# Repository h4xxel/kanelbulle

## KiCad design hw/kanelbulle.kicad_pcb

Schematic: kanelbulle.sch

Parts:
C1, C2, C3, C4, C5, C6, C7, C8: C
D1, D2, D3, D4, D5, D6, D7, D8, D9, D10, D11, D12, D13, D14, D15, D16, D17, D18, D19, D20, D21, D22, D23, D24, D25, D26, D27, D28, D29, D30, D31, D32, D33, D34, D35, D36, D37, D38, D39, D40, D41, D42, D43, D44, D45, D46, D47, D48, D49, D50, D51: LED_RGB
P1: USB
P2: CONN_6
R1, R2, R3, R4, R5, R6, R7, R8, R9, R10, R11, R12, R13, R14, R15, R16, R17, R18, R19: R
U1: LPC1114/302
U2: PCA9685
U3, U4, U5: ULN2003A
U6: NCP1117ST33T3G

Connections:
3V3: C1.1, C2.1, C3.1, C4.1, C5.1, C6.1, C7.1, D1.1 (A), D2.1 (A), D3.1 (A), D4.1 (A), D5.1 (A), D6.1 (A), D7.1 (A), D8.1 (A), D9.1 (A), D10.1 (A), D11.1 (A), D12.1 (A), D13.1 (A), D14.1 (A), D15.1 (A), D16.1 (A), D17.1 (A), D18.1 (A), D19.1 (A), D20.1 (A), D21.1 (A), D22.1 (A), D23.1 (A), D24.1 (A), D25.1 (A), D26.1 (A), D27.1 (A), D28.1 (A), D29.1 (A), D30.1 (A), D31.1 (A), D32.1 (A), D33.1 (A), D34.1 (A), D35.1 (A), D36.1 (A), D37.1 (A), D38.1 (A), D39.1 (A), D40.1 (A), D41.1 (A), D42.1 (A), D43.1 (A), D44.1 (A), D45.1 (A), D46.1 (A), D47.1 (A), D48.1 (A), D49.1 (A), D50.1 (A), D51.1 (A), P2.6, R1.1, R2.1, R3.1, R4.1, U1.8 (VDD), U1.44 (VDD), U2.1 (A0), U2.3 (A2), U2.5 (A4), U2.28 (VDD), U6.2 (VO)
+5V: C8.1, P1.4, U6.3 (VI)
/B1: D1.4 (B), D2.4 (B), D3.4 (B), D4.4 (B), D5.4 (B), D6.4 (B), D7.4 (B), D8.4 (B), D9.4 (B), D10.4 (B), D11.4 (B), D12.4 (B), D13.4 (B), D14.4 (B), D15.4 (B), D16.4 (B), D17.4 (B), D18.4 (B), D19.4 (B), D20.4 (B), R15.2
/B2: D21.4 (B), D22.4 (B), D23.4 (B), D24.4 (B), D25.4 (B), D26.4 (B), D27.4 (B), D28.4 (B), D29.4 (B), D30.4 (B), D31.4 (B), D32.4 (B), D33.4 (B), D34.4 (B), D35.4 (B), R16.2
/B3: D36.4 (B), D37.4 (B), D38.4 (B), D39.4 (B), D40.4 (B), D41.4 (B), D42.4 (B), D43.4 (B), D44.4 (B), D45.4 (B), R17.2
/B4: D46.4 (B), D47.4 (B), D48.4 (B), D49.4 (B), D50.4 (B), R18.2
/B5: D51.4 (B), R19.2
/G1: D1.3 (G), D2.3 (G), D3.3 (G), D4.3 (G), D5.3 (G), D6.3 (G), D7.3 (G), D8.3 (G), D9.3 (G), D10.3 (G), D11.3 (G), D12.3 (G), D13.3 (G), D14.3 (G), D15.3 (G), D16.3 (G), D17.3 (G), D18.3 (G), D19.3 (G), D20.3 (G), R10.2
/G2: D21.3 (G), D22.3 (G), D23.3 (G), D24.3 (G), D25.3 (G), D26.3 (G), D27.3 (G), D28.3 (G), D29.3 (G), D30.3 (G), D31.3 (G), D32.3 (G), D33.3 (G), D34.3 (G), D35.3 (G), R11.2
/G3: D36.3 (G), D37.3 (G), D38.3 (G), D39.3 (G), D40.3 (G), D41.3 (G), D42.3 (G), D43.3 (G), D44.3 (G), D45.3 (G), R12.2
/G4: D46.3 (G), D47.3 (G), D48.3 (G), D49.3 (G), D50.3 (G), R13.2
/G5: D51.3 (G), R14.2
/ISP: P2.2, R1.2, U1.4 (~ISP_EN)
/LEDOE: U1.14 (PIO0_3), U2.23 (~OE)
/R1: D1.2 (R), D2.2 (R), D3.2 (R), D4.2 (R), D5.2 (R), D6.2 (R), D7.2 (R), D8.2 (R), D9.2 (R), D10.2 (R), D11.2 (R), D12.2 (R), D13.2 (R), D14.2 (R), D15.2 (R), D16.2 (R), D17.2 (R), D18.2 (R), D19.2 (R), D20.2 (R), R5.2
/R2: D21.2 (R), D22.2 (R), D23.2 (R), D24.2 (R), D25.2 (R), D26.2 (R), D27.2 (R), D28.2 (R), D29.2 (R), D30.2 (R), D31.2 (R), D32.2 (R), D33.2 (R), D34.2 (R), D35.2 (R), R6.2
/R3: D36.2 (R), D37.2 (R), D38.2 (R), D39.2 (R), D40.2 (R), D41.2 (R), D42.2 (R), D43.2 (R), D44.2 (R), D45.2 (R), R7.2
/R4: D46.2 (R), D47.2 (R), D48.2 (R), D49.2 (R), D50.2 (R), R8.2
/R5: D51.2 (R), R9.2
/RST: P2.1, R2.2, U1.3 (~RESET)
/RX: P2.4, U1.46 (PIO1_6/RXD)
/SCL: R4.2, U1.15 (PIO0_4), U2.26 (SCL)
/SDA: R3.2, U1.16 (PIO0_5), U2.27 (SDA)
/TX: P2.3, U1.47 (PIO1_7/TXD)
GND: C1.2, C2.2, C3.2, C4.2, C5.2, C6.2, C7.2, C8.2, P1.1, P1.GND, P2.5, U1.5 (VSS), U1.41 (VSS), U2.2 (A1), U2.4 (A3), U2.14 (VSS), U2.24 (A5), U2.25 (EXTCLK), U3.6 (I6), U3.7 (I7), U3.8 (GND), U4.6 (I6), U4.7 (I7), U4.8 (GND), U5.6 (I6), U5.7 (I7), U5.8 (GND), U6.1 (GND)
unnamed: R14.1, U4.12 (O5)
unnamed: R5.1, U3.16 (O1)
unnamed: R6.1, U3.15 (O2)
unnamed: R7.1, U3.14 (O3)
unnamed: R8.1, U3.13 (O4)
unnamed: R9.1, U3.12 (O5)
unnamed: R10.1, U4.16 (O1)
unnamed: R11.1, U4.15 (O2)
unnamed: R12.1, U4.14 (O3)
unnamed: R13.1, U4.13 (O4)
unnamed: U2.7 (LED1), U3.2 (I2)
unnamed: U2.6 (LED0), U3.1 (I1)
unnamed: U2.11 (LED5), U4.1 (I1)
unnamed: U2.10 (LED4), U3.5 (I5)
unnamed: U2.9 (LED3), U3.4 (I4)
unnamed: U2.8 (LED2), U3.3 (I3)
unnamed: R15.1, U5.16 (O1)
unnamed: R16.1, U5.15 (O2)
unnamed: U2.15 (LED8), U4.4 (I4)
unnamed: U2.18 (LED11), U5.2 (I2)
unnamed: U2.17 (LED10), U5.1 (I1)
unnamed: U2.16 (LED9), U4.5 (I5)
unnamed: U2.13 (LED7), U4.3 (I3)
unnamed: U2.12 (LED6), U4.2 (I2)
unnamed: U2.21 (LED14), U5.5 (I5)
unnamed: U2.20 (LED13), U5.4 (I4)
unnamed: U2.19 (LED12), U5.3 (I3)
unnamed: R19.1, U5.12 (O5)
unnamed: R18.1, U5.13 (O4)
unnamed: R17.1, U5.14 (O3)

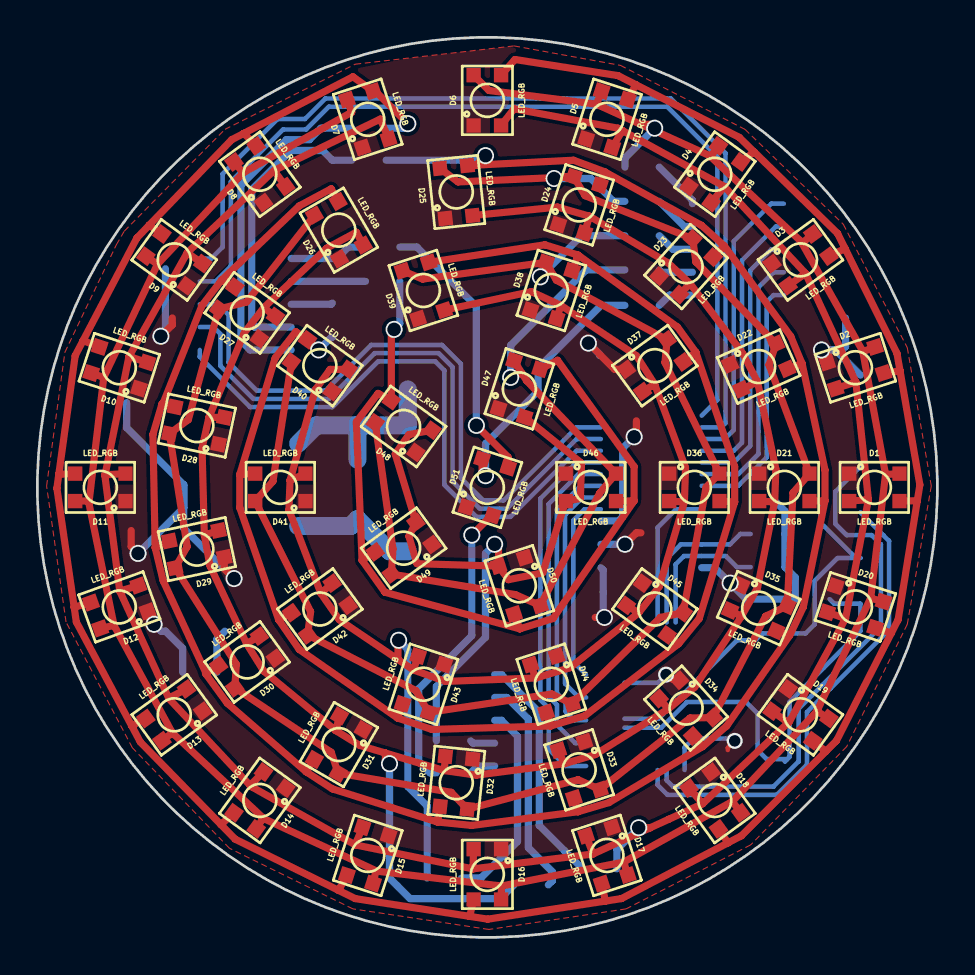
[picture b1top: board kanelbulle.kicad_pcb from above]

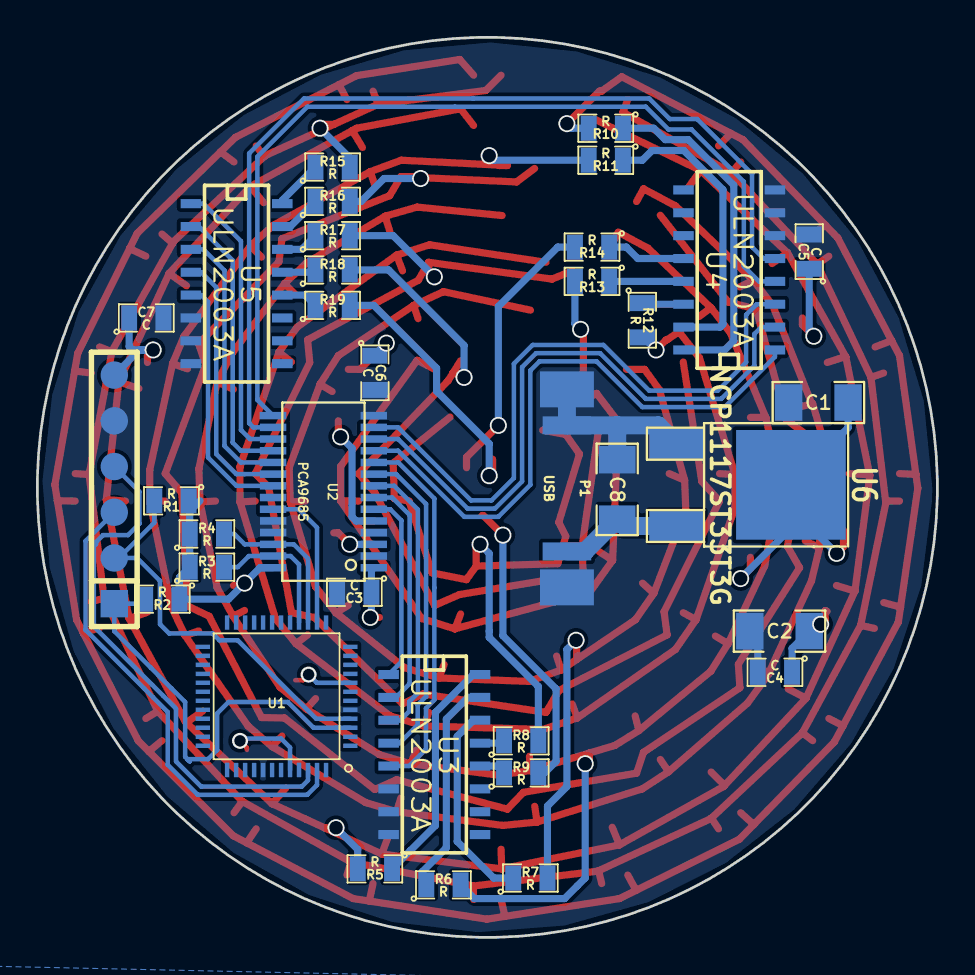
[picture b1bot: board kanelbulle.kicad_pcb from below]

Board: 2 copper layers, 50.0 x 50.0 mm, 86 parts (35 on the bottom side), 55 nets.

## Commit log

2015-01-28 gitignore
2015-01-28 hardware placeholder
2015-01-28 added micro controller to schematic
2015-01-28 leds, leds everywhere
2015-01-29 added led driver chip
2015-01-29 added led 3d model
2015-01-29 lqfp 3d model
2015-02-01 Moved all LEDs
2015-02-02 connected leds on schematic
2015-02-02 directory structure
2015-02-02 mit licence
2015-02-02 LED alignment coordinate tool added
2015-02-02 moved leds away from edge
2015-02-02 connected leds to eachother
2015-02-02 connected some OC drivers
2015-02-02 decoupling
2015-02-03 3d renders
2015-02-03 aaawww yeeeeaaaahhhh
2015-02-03 gerber plot
2015-02-06 renders
2015-02-10 Started on i2c stuff
2015-03-02 atoi added
2015-03-02 Fix build
2015-03-02 parse commands from uart
2015-03-02 cleaned up code base
2015-03-02 ack serial
2015-03-02 nack invalid commands
2015-03-02 trig 100 times a second
2015-03-02 arne
2015-03-02 nak commands during special effect
2015-03-02 oops
